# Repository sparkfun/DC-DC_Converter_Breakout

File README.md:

SparkFun DC/DC Converter Breakout
========================================

[*SparkFun DC/DC Converter Breakout (BOB-09370)*](https://www.sparkfun.com/products/9370)

This is a breakout board for our non-isolated, 6A DC-to-DC Converter Module. 
The module can convert any DC voltage between 4.5-14VDC to a selectable voltage between 0.59 and 5.5VDC.

Repository Contents
-------------------

* **/Hardware** - Eagle design files (.brd, .sch)
* **/Production** - Production panel files (.brd)

Documentation
--------------
* **[SparkFun Fritzing repo](https://github.com/sparkfun/Fritzing_Parts)** - Fritzing diagrams for SparkFun products.
* **[SparkFun 3D Model repo](https://github.com/sparkfun/3D_Models)** - 3D models of SparkFun products. 

License Information
-------------------
This product is _**open source**_! 

The **hardware** is released under [Creative Commons ShareAlike 4.0 International](https://creativecommons.org/licenses/by-sa/4.0/).

Please use, reuse, and modify these files as you see fit. Please maintain attribution to SparkFun Electronics and release anything derivative under the same license.

Distributed as-is; no warranty is given.

- Your friends at SparkFun.

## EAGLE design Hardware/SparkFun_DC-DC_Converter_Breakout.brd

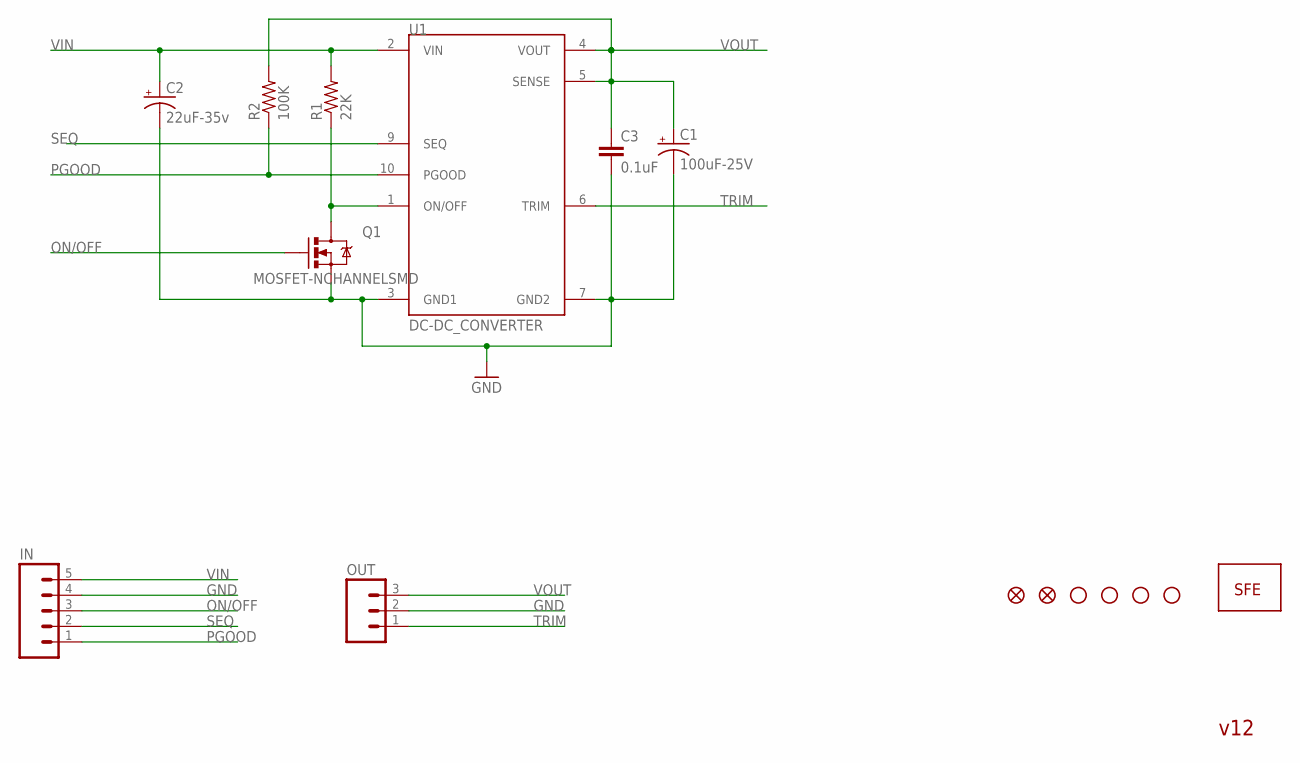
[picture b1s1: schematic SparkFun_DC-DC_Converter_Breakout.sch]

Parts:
C1: 100uF-25V; NIPPON_F80
C2: 22uF-35v; PANASONIC_C
C3: 0.1uF; 0603-CAP
FID1, FID2: FIDUCIAL1X2; FIDUCIAL-1X2
IN: M05PTH; 1X05
OUT: M03PTH; 1X03
Q1: MOSFET-NCHANNELSMD; SOT23-3
R1: 22K; 0603-RES
R2: 100K; 0603-RES
U1: DC-DC_CONVERTER
U$1, U$3, U$4, U$5: STAND-OFF
U$2: LOGO-SFENEW; SFE-NEW-WEBLOGO

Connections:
GND: C1.-, C2.-, C3.2, IN.4, OUT.2, Q1.2 (S), U1.3 (GND1), U1.7 (GND2)
unnamed: Q1.3 (D), R1.1, U1.1 (ON/OFF)
ON/OFF: IN.3, Q1.1 (G)
PGOOD: IN.1, R2.1, U1.10 (PGOOD)
SEQ: IN.2, U1.9 (SEQ)
TRIM: OUT.1, U1.6 (TRIM)
VIN: C2.+, IN.5, R1.2, U1.2 (VIN)
VOUT: C1.+, C3.1, OUT.3, R2.2, U1.4 (VOUT), U1.5 (SENSE)

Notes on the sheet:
v12

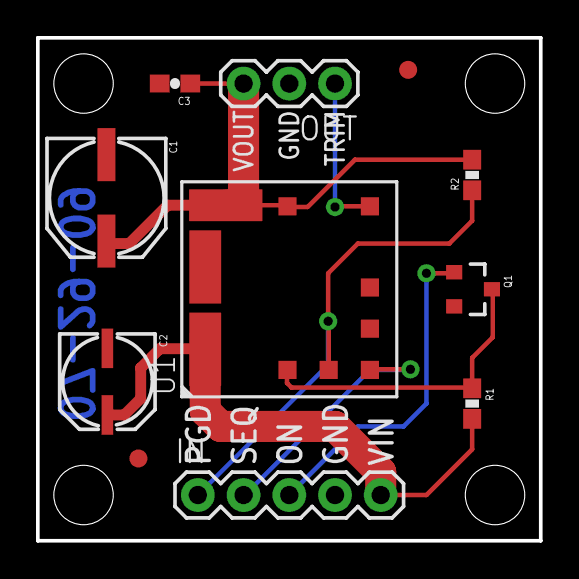
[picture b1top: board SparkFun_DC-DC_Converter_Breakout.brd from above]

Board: 2 copper layers, 27.9 x 27.9 mm, 16 parts (1 on the bottom side), 8 nets.

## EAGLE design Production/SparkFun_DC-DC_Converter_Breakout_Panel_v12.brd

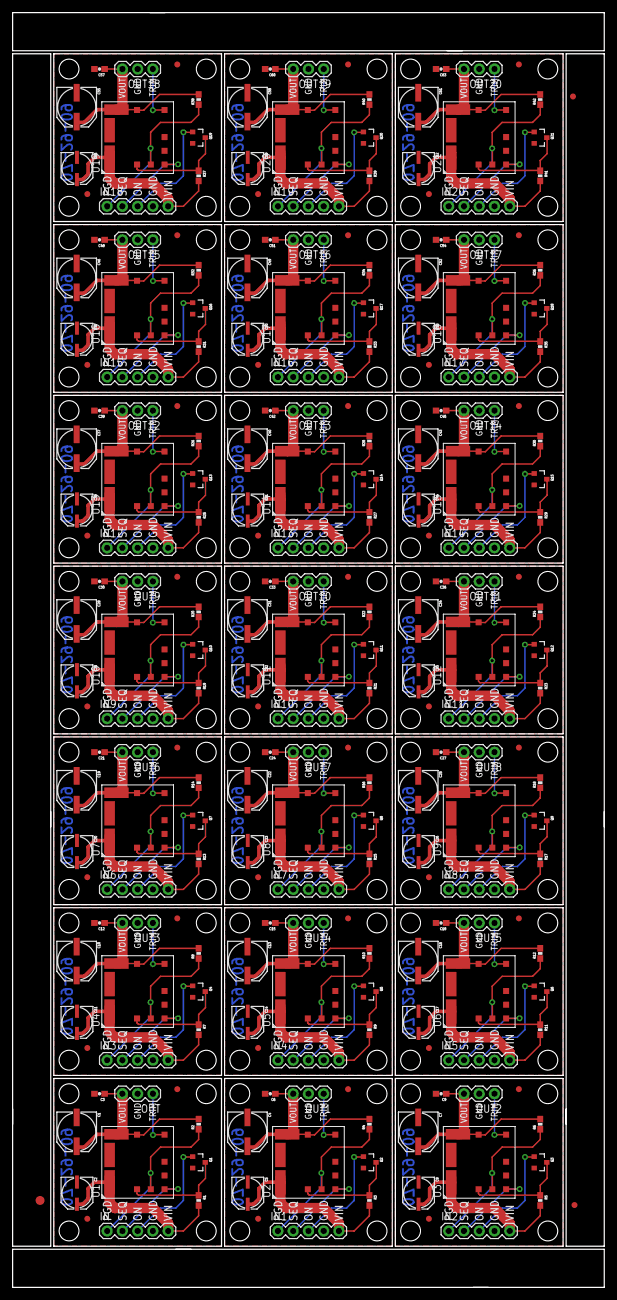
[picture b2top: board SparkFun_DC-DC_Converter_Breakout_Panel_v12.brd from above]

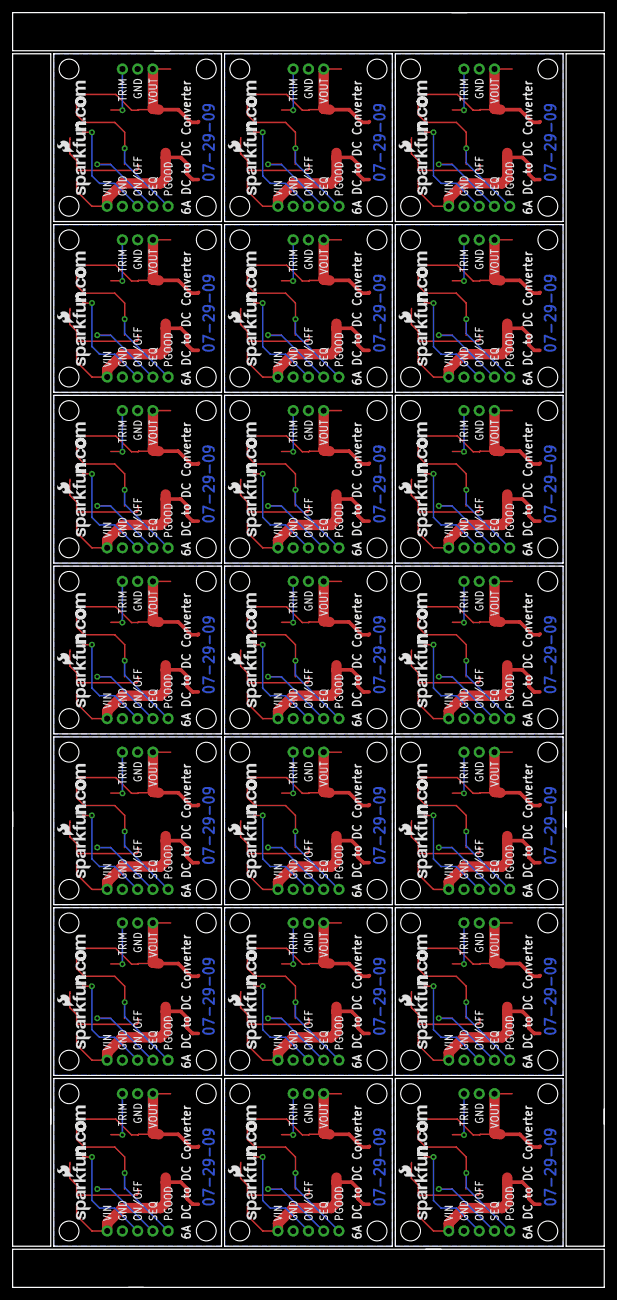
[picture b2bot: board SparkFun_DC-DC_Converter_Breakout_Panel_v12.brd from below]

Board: 2 copper layers, 98.6 x 212.3 mm, 339 parts (21 on the bottom side), 168 nets.

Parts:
C1, C4, C7, C10, C13, C16, C19, C22, C25, C28, C31, C34, C37, C40, C43, C46, C49, C52, C55, C58, C61: 100uF-25V; NIPPON_F80
C2, C5, C8, C11, C14, C17, C20, C23, C26, C29, C32, C35, C38, C41, C44, C47, C50, C53, C56, C59, C62: 22uF-35v; PANASONIC_C
C3, C6, C9, C12, C15, C18, C21, C24, C27, C30, C33, C36, C39, C42, C45, C48, C51, C54, C57, C60, C63: 0.1uF; 0603-CAP
E$1, E$5: FIDUCIAL-1X2
E$2: FIDUCIAL-1.5X3
FID1, FID2, FID3, FID4, FID5, FID6, FID7, FID8, FID9, FID10, FID11, FID12, FID13, FID14, FID15, FID16, FID17, FID18, FID19, FID20, FID21, FID22, FID23, FID24, FID25, FID26, FID27, FID28, FID29, FID30, FID31, FID32, FID33, FID34, FID35, FID36, FID37, FID38, FID39, FID40, FID41, FID42: FIDUCIAL1X2; FIDUCIAL-1X2
IN, IN1, IN2, IN3, IN4, IN5, IN6, IN7, IN8, IN9, IN10, IN11, IN12, IN13, IN14, IN15, IN16, IN17, IN18, IN19, IN20: 1X05
OUT, OUT1, OUT2, OUT3, OUT4, OUT5, OUT6, OUT7, OUT8, OUT9, OUT10, OUT11, OUT12, OUT13, OUT14, OUT15, OUT16, OUT17, OUT18, OUT19, OUT20: 1X03
Q1, Q2, Q3, Q4, Q5, Q6, Q7, Q8, Q9, Q10, Q11, Q12, Q13, Q14, Q15, Q16, Q17, Q18, Q19, Q20, Q21: MOSFET-NCHANNELSMD; SOT23-3
R1, R3, R5, R7, R9, R11, R13, R15, R17, R19, R21, R23, R25, R27, R29, R31, R33, R35, R37, R39, R41: 22K; 0603-RES
R2, R4, R6, R8, R10, R12, R14, R16, R18, R20, R22, R24, R26, R28, R30, R32, R34, R36, R38, R40, R42: 100K; 0603-RES
U1, U2, U3, U4, U5, U6, U7, U8, U9, U10, U11, U12, U13, U14, U15, U16, U17, U18, U19, U20, U21: DC-DC_CONVERTER
U$1, U$3, U$4, U$5, U$7, U$8, U$9, U$10, U$12, U$13, U$14, U$15, U$17, U$18, U$19, U$20, U$22, U$23, U$24, U$25, U$27, U$28, U$29, U$30, U$32, U$33, U$34, U$35, U$37, U$38, U$39, U$40, U$42, U$43, U$44, U$45, U$47, U$48, U$49, U$50, U$52, U$53, U$54, U$55, U$57, U$58, U$59, U$60, U$62, U$63, U$64, U$65, U$67, U$68, U$69, U$70, U$72, U$73, U$74, U$75, U$77, U$78, U$79, U$80, U$82, U$83, U$84, U$85, U$87, U$88, U$89, U$90, U$92, U$93, U$94, U$95, U$97, U$98, U$99, U$100, U$102, U$103, U$104, U$105: STAND-OFF
U$2, U$6, U$11, U$16, U$21, U$26, U$31, U$36, U$41, U$46, U$51, U$56, U$61, U$66, U$71, U$76, U$81, U$86, U$91, U$96, U$101: LOGO-SFENEW; SFE-NEW-WEBLOGO

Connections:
GND: C1.-, C2.-, C3.2, IN.4, OUT.2, Q1.2, U1.3, U1.7
GND1: C4.-, C5.-, C6.2, IN1.4, OUT1.2, Q2.2, U2.3, U2.7
GND2: C7.-, C8.-, C9.2, IN2.4, OUT2.2, Q3.2, U3.3, U3.7
GND3: C10.-, C11.-, C12.2, IN3.4, OUT3.2, Q4.2, U4.3, U4.7
GND4: C13.-, C14.-, C15.2, IN4.4, OUT4.2, Q5.2, U5.3, U5.7
GND5: C16.-, C17.-, C18.2, IN5.4, OUT5.2, Q6.2, U6.3, U6.7
GND6: C19.-, C20.-, C21.2, IN6.4, OUT6.2, Q7.2, U7.3, U7.7
GND7: C22.-, C23.-, C24.2, IN7.4, OUT7.2, Q8.2, U8.3, U8.7
GND8: C25.-, C26.-, C27.2, IN8.4, OUT8.2, Q9.2, U9.3, U9.7
GND9: C28.-, C29.-, C30.2, IN9.4, OUT9.2, Q10.2, U10.3, U10.7
GND10: C31.-, C32.-, C33.2, IN10.4, OUT10.2, Q11.2, U11.3, U11.7
GND11: C34.-, C35.-, C36.2, IN11.4, OUT11.2, Q12.2, U12.3, U12.7
GND12: C37.-, C38.-, C39.2, IN12.4, OUT12.2, Q13.2, U13.3, U13.7
GND13: C40.-, C41.-, C42.2, IN13.4, OUT13.2, Q14.2, U14.3, U14.7
GND14: C43.-, C44.-, C45.2, IN14.4, OUT14.2, Q15.2, U15.3, U15.7
GND15: C46.-, C47.-, C48.2, IN15.4, OUT15.2, Q16.2, U16.3, U16.7
GND16: C49.-, C50.-, C51.2, IN16.4, OUT16.2, Q17.2, U17.3, U17.7
GND17: C52.-, C53.-, C54.2, IN17.4, OUT17.2, Q18.2, U18.3, U18.7
GND18: C55.-, C56.-, C57.2, IN18.4, OUT18.2, Q19.2, U19.3, U19.7
GND19: C58.-, C59.-, C60.2, IN19.4, OUT19.2, Q20.2, U20.3, U20.7
GND20: C61.-, C62.-, C63.2, IN20.4, OUT20.2, Q21.2, U21.3, U21.7
unnamed: Q1.3, R1.1, U1.1
unnamed: Q2.3, R3.1, U2.1
unnamed: Q3.3, R5.1, U3.1
unnamed: Q4.3, R7.1, U4.1
unnamed: Q5.3, R9.1, U5.1
unnamed: Q6.3, R11.1, U6.1
unnamed: Q7.3, R13.1, U7.1
unnamed: Q8.3, R15.1, U8.1
unnamed: Q9.3, R17.1, U9.1
unnamed: Q10.3, R19.1, U10.1
unnamed: Q11.3, R21.1, U11.1
unnamed: Q12.3, R23.1, U12.1
unnamed: Q13.3, R25.1, U13.1
unnamed: Q14.3, R27.1, U14.1
unnamed: Q15.3, R29.1, U15.1
unnamed: Q16.3, R31.1, U16.1
unnamed: Q17.3, R33.1, U17.1
unnamed: Q18.3, R35.1, U18.1
unnamed: Q19.3, R37.1, U19.1
unnamed: Q20.3, R39.1, U20.1
unnamed: Q21.3, R41.1, U21.1
ON/OFF: IN.3, Q1.1
ON/OFF1: IN1.3, Q2.1
ON/OFF2: IN2.3, Q3.1
ON/OFF3: IN3.3, Q4.1
ON/OFF4: IN4.3, Q5.1
ON/OFF5: IN5.3, Q6.1
ON/OFF6: IN6.3, Q7.1
ON/OFF7: IN7.3, Q8.1
ON/OFF8: IN8.3, Q9.1
ON/OFF9: IN9.3, Q10.1
ON/OFF10: IN10.3, Q11.1
ON/OFF11: IN11.3, Q12.1
ON/OFF12: IN12.3, Q13.1
ON/OFF13: IN13.3, Q14.1
ON/OFF14: IN14.3, Q15.1
ON/OFF15: IN15.3, Q16.1
ON/OFF16: IN16.3, Q17.1
ON/OFF17: IN17.3, Q18.1
ON/OFF18: IN18.3, Q19.1
ON/OFF19: IN19.3, Q20.1
ON/OFF20: IN20.3, Q21.1
PGOOD: IN.1, R2.1, U1.10
PGOOD1: IN1.1, R4.1, U2.10
PGOOD2: IN2.1, R6.1, U3.10
PGOOD3: IN3.1, R8.1, U4.10
PGOOD4: IN4.1, R10.1, U5.10
PGOOD5: IN5.1, R12.1, U6.10
PGOOD6: IN6.1, R14.1, U7.10
PGOOD7: IN7.1, R16.1, U8.10
PGOOD8: IN8.1, R18.1, U9.10
PGOOD9: IN9.1, R20.1, U10.10
PGOOD10: IN10.1, R22.1, U11.10
PGOOD11: IN11.1, R24.1, U12.10
PGOOD12: IN12.1, R26.1, U13.10
PGOOD13: IN13.1, R28.1, U14.10
PGOOD14: IN14.1, R30.1, U15.10
PGOOD15: IN15.1, R32.1, U16.10
PGOOD16: IN16.1, R34.1, U17.10
PGOOD17: IN17.1, R36.1, U18.10
PGOOD18: IN18.1, R38.1, U19.10
PGOOD19: IN19.1, R40.1, U20.10
PGOOD20: IN20.1, R42.1, U21.10
SEQ: IN.2, U1.9
SEQ1: IN1.2, U2.9
SEQ2: IN2.2, U3.9
SEQ3: IN3.2, U4.9
SEQ4: IN4.2, U5.9
SEQ5: IN5.2, U6.9
SEQ6: IN6.2, U7.9
SEQ7: IN7.2, U8.9
SEQ8: IN8.2, U9.9
SEQ9: IN9.2, U10.9
SEQ10: IN10.2, U11.9
SEQ11: IN11.2, U12.9
SEQ12: IN12.2, U13.9
SEQ13: IN13.2, U14.9
SEQ14: IN14.2, U15.9
SEQ15: IN15.2, U16.9
SEQ16: IN16.2, U17.9
SEQ17: IN17.2, U18.9
SEQ18: IN18.2, U19.9
SEQ19: IN19.2, U20.9
SEQ20: IN20.2, U21.9
TRIM: OUT.1, U1.6
TRIM1: OUT1.1, U2.6
TRIM2: OUT2.1, U3.6
TRIM3: OUT3.1, U4.6
TRIM4: OUT4.1, U5.6
TRIM5: OUT5.1, U6.6
TRIM6: OUT6.1, U7.6
TRIM7: OUT7.1, U8.6
TRIM8: OUT8.1, U9.6
TRIM9: OUT9.1, U10.6
TRIM10: OUT10.1, U11.6
TRIM11: OUT11.1, U12.6
TRIM12: OUT12.1, U13.6
TRIM13: OUT13.1, U14.6
TRIM14: OUT14.1, U15.6
TRIM15: OUT15.1, U16.6
TRIM16: OUT16.1, U17.6
TRIM17: OUT17.1, U18.6
TRIM18: OUT18.1, U19.6
TRIM19: OUT19.1, U20.6
TRIM20: OUT20.1, U21.6
VIN: C2.+, IN.5, R1.2, U1.2
VIN1: C5.+, IN1.5, R3.2, U2.2
VIN2: C8.+, IN2.5, R5.2, U3.2
VIN3: C11.+, IN3.5, R7.2, U4.2
VIN4: C14.+, IN4.5, R9.2, U5.2
VIN5: C17.+, IN5.5, R11.2, U6.2
VIN6: C20.+, IN6.5, R13.2, U7.2
VIN7: C23.+, IN7.5, R15.2, U8.2
VIN8: C26.+, IN8.5, R17.2, U9.2
VIN9: C29.+, IN9.5, R19.2, U10.2
VIN10: C32.+, IN10.5, R21.2, U11.2
VIN11: C35.+, IN11.5, R23.2, U12.2
VIN12: C38.+, IN12.5, R25.2, U13.2
VIN13: C41.+, IN13.5, R27.2, U14.2
VIN14: C44.+, IN14.5, R29.2, U15.2
VIN15: C47.+, IN15.5, R31.2, U16.2
VIN16: C50.+, IN16.5, R33.2, U17.2
VIN17: C53.+, IN17.5, R35.2, U18.2
VIN18: C56.+, IN18.5, R37.2, U19.2
VIN19: C59.+, IN19.5, R39.2, U20.2
VIN20: C62.+, IN20.5, R41.2, U21.2
VOUT: C1.+, C3.1, OUT.3, R2.2, U1.4, U1.5
VOUT1: C4.+, C6.1, OUT1.3, R4.2, U2.4, U2.5
VOUT2: C7.+, C9.1, OUT2.3, R6.2, U3.4, U3.5
VOUT3: C10.+, C12.1, OUT3.3, R8.2, U4.4, U4.5
VOUT4: C13.+, C15.1, OUT4.3, R10.2, U5.4, U5.5
VOUT5: C16.+, C18.1, OUT5.3, R12.2, U6.4, U6.5
VOUT6: C19.+, C21.1, OUT6.3, R14.2, U7.4, U7.5
VOUT7: C22.+, C24.1, OUT7.3, R16.2, U8.4, U8.5
VOUT8: C25.+, C27.1, OUT8.3, R18.2, U9.4, U9.5
VOUT9: C28.+, C30.1, OUT9.3, R20.2, U10.4, U10.5
VOUT10: C31.+, C33.1, OUT10.3, R22.2, U11.4, U11.5
VOUT11: C34.+, C36.1, OUT11.3, R24.2, U12.4, U12.5
VOUT12: C37.+, C39.1, OUT12.3, R26.2, U13.4, U13.5
VOUT13: C40.+, C42.1, OUT13.3, R28.2, U14.4, U14.5
VOUT14: C43.+, C45.1, OUT14.3, R30.2, U15.4, U15.5
VOUT15: C46.+, C48.1, OUT15.3, R32.2, U16.4, U16.5
VOUT16: C49.+, C51.1, OUT16.3, R34.2, U17.4, U17.5
VOUT17: C52.+, C54.1, OUT17.3, R36.2, U18.4, U18.5
VOUT18: C55.+, C57.1, OUT18.3, R38.2, U19.4, U19.5
VOUT19: C58.+, C60.1, OUT19.3, R40.2, U20.4, U20.5
VOUT20: C61.+, C63.1, OUT20.3, R42.2, U21.4, U21.5

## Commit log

2015-05-07 Adding hardware files
2015-10-20 added local fiducials
2015-10-20 created panel v12

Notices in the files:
parts and their libraries:
SparkFun-Aesthetics: Licensing: Creative Commons ShareAlike 4.0 International - https://creativecommons.org/licenses/by-sa/4.0
